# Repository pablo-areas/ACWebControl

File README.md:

# ACWebControl
Air Conditioning web control for BGH BSI35WCGT, remote control RG10A(E2S)/BGEF.

Server running on [ESP8266](https://github.com/NicoThien/IRremoteESP8266/blob/master/examples/Web-AC-control/Web-AC-control.ino).

On/off , mode, fan flow and temperature control. Off timer with 3 presets, and display disable function.

Ambient temperature sensor DS18B20. Responsive interface.

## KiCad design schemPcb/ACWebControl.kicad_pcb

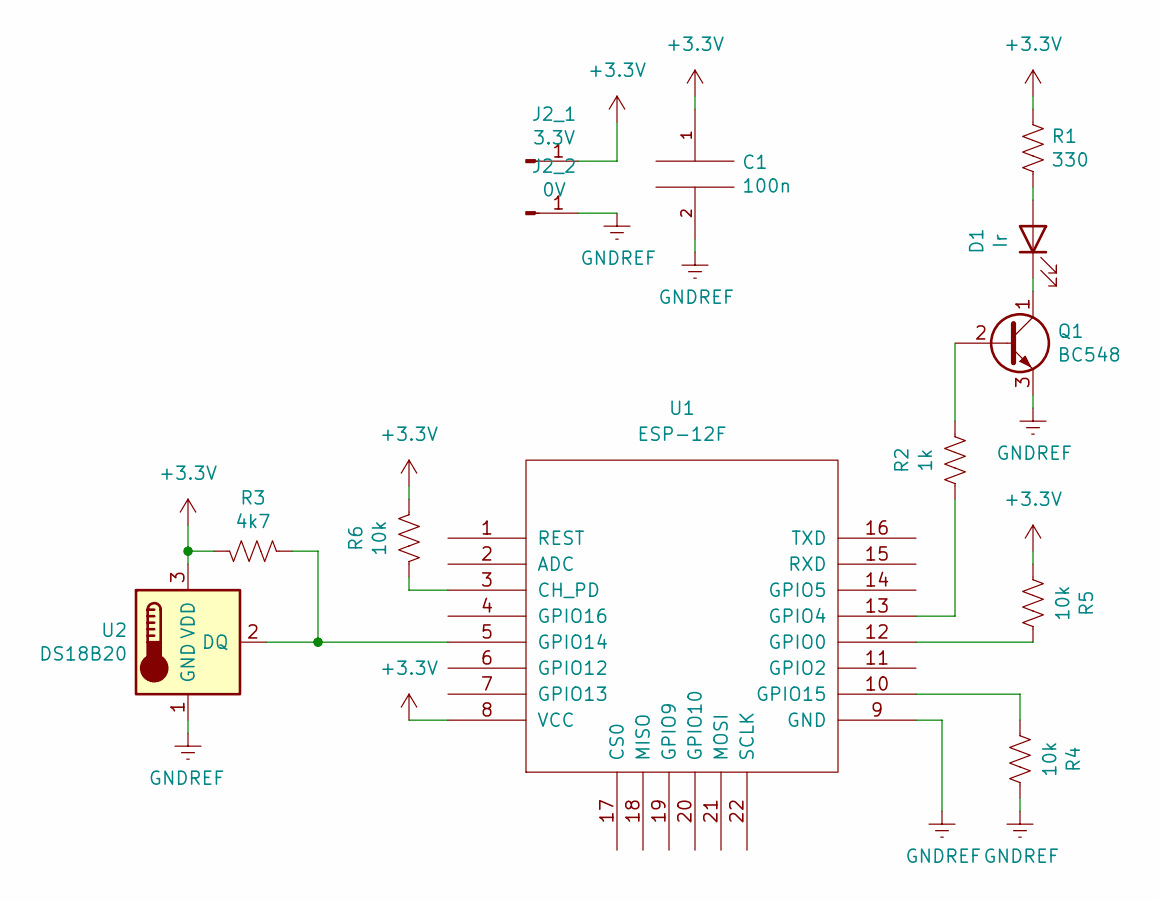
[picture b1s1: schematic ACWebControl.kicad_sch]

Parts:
C1: 100n; C_Disc_D5.0mm_W2.5mm_P5.00mm
D1: Ir; LED_D5.0mm
J2_1: 3.3V; Pin_D1.1mm_L8.5mm_W2.5mm_FlatFork
J2_2: 0V; Pin_D1.1mm_L8.5mm_W2.5mm_FlatFork
Q1: BC548; TO-92_Inline
R1: 330; R_Axial_DIN0207_L6.3mm_D2.5mm_P7.62mm_Horizontal
R2: 1k; R_Axial_DIN0207_L6.3mm_D2.5mm_P7.62mm_Horizontal
R3: 4k7; R_Axial_DIN0207_L6.3mm_D2.5mm_P7.62mm_Horizontal
R4, R5, R6: 10k; R_Axial_DIN0207_L6.3mm_D2.5mm_P7.62mm_Horizontal
U1: ESP-12F; ESP-12E
U2: DS18B20; TO-92_Inline

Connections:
+3.3V: C1.1, J2_1.1, R1.1, R3.1, R5.2, R6.2, U1.8 (VCC), U2.3 (VDD)
GNDREF: C1.2, J2_2.1, Q1.3 (E), R4.1, U1.9 (GND), U2.1 (GND)
unnamed: D1.1 (K), Q1.1 (C)
unnamed: D1.2 (A), R1.2
unnamed: Q1.2 (B), R2.1
unnamed: R2.2, U1.13 (GPIO4)
unnamed: R3.2, U1.5 (GPIO14), U2.2 (DQ)
unnamed: R4.2, U1.10 (GPIO15)
unnamed: R5.1, U1.12 (GPIO0)
unnamed: R6.1, U1.3 (CH_PD)

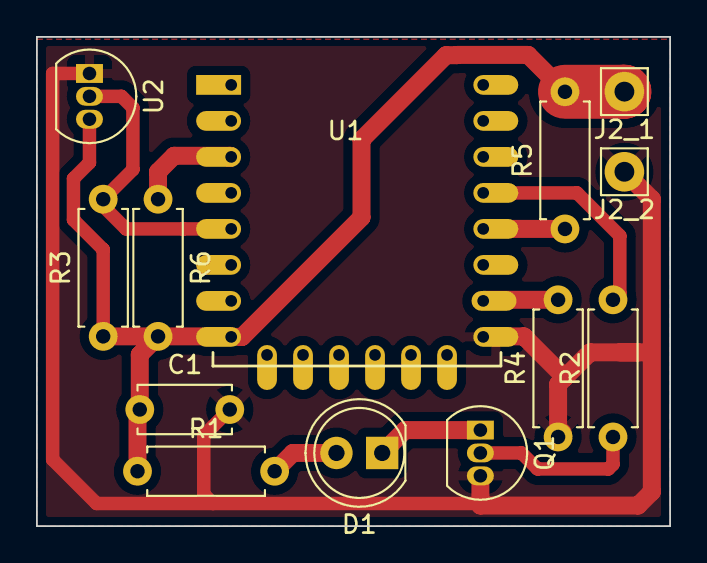
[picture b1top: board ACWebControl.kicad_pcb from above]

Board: 2 copper layers, 35.2 x 27.2 mm, 13 parts (0 on the bottom side), 10 nets.
